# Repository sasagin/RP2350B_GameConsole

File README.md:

For Retrogame
Vtech Creativision  https://github.com/sasagin/Creativision

ColecoVision        https://github.com/sasagin/ColecoRP2350B

SEGA SG1000         https://github.com/sasagin/SG1000

https://github.com/visrealm/pico9918/releases

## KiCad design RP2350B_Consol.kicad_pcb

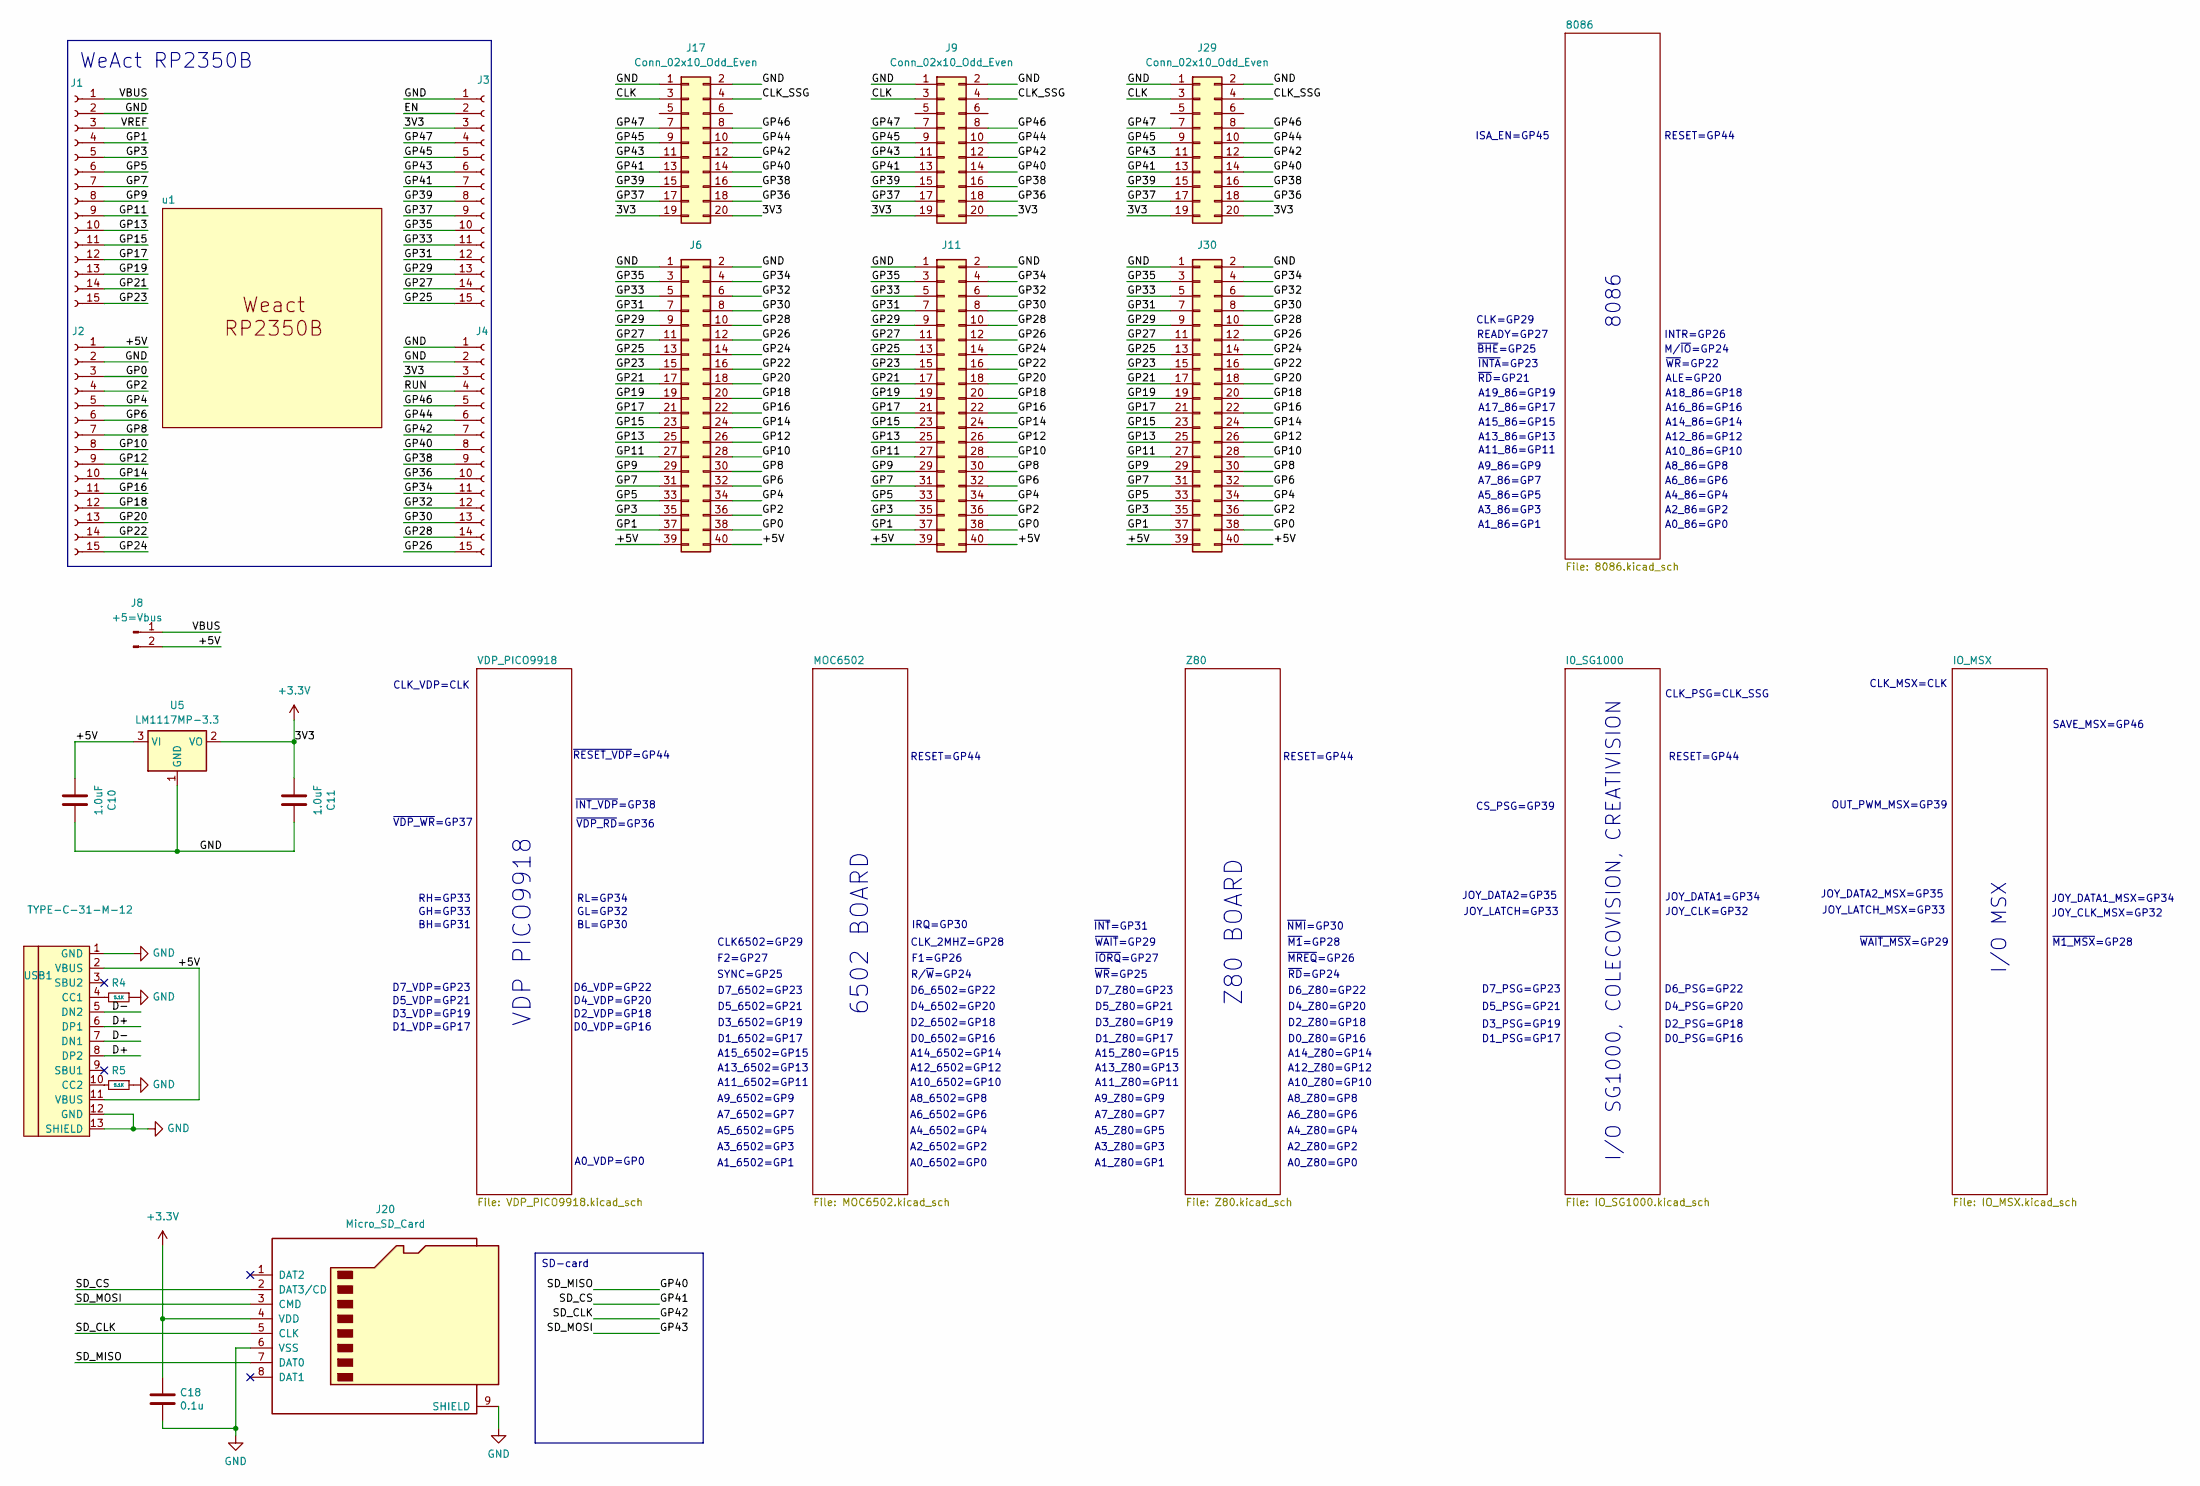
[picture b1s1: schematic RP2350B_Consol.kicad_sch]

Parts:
C10, C11: 1.0uF; C_0805_2012Metric_Pad1.18x1.45mm_HandSolder; DigiKey 1276-1099-1-ND
C18: 0.1u; C_0805_2012Metric_Pad1.18x1.45mm_HandSolder
J1, J2, J3, J4: Conn_01x15_Socket; PinSocket_1x15_P2.54mm_Vertical
J6, J11, J30: Conn_02x20_Odd_Even; PinSocket_2x20_P2.54mm_Vertical
J8: +5=Vbus; PinHeader_1x02_P2.54mm_Vertical
J9, J17, J29: Conn_02x10_Odd_Even; PinSocket_2x10_P2.54mm_Vertical
J20: Micro_SD_Card; GCT-MEM2055-00-190-01-A
R4, R5: 5.1K; R_0805_2012Metric_Pad1.20x1.40mm_HandSolder
U5: LM1117MP-3.3; SOT-223-3_TabPin2
USB1: TYPE-C-31-M-12; USB-TYPE-C-31-M-12_lib2; LCSC C165948
u1: RP2350B_WeAct

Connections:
+3.3V: C11.2, C18.1, J3.3, J4.3, J9.19, J9.20, J17.19, J17.20, J20.4 (VDD), J29.19, J29.20, U5.2 (VO)
/+5V: C10.2, J2.1, J6.39, J6.40, J8.2, J11.39, J11.40, J30.39, J30.40, U5.3 (VI), USB1.2 (VBUS), USB1.11 (VBUS)
/CLK: J9.3, J17.3, J29.3
/CLK_SSG: J9.4, J17.4, J29.4
/D+: USB1.6 (DP1), USB1.8 (DP2)
/D-: USB1.5 (DN2), USB1.7 (DN1)
/EN: J3.2
/GP0: J2.3, J6.38, J11.38, J30.38
/GP1: J1.4, J6.37, J11.37, J30.37
/GP2: J2.4, J6.36, J11.36, J30.36
/GP3: J1.5, J6.35, J11.35, J30.35
/GP4: J2.5, J6.34, J11.34, J30.34
/GP5: J1.6, J6.33, J11.33, J30.33
/GP6: J2.6, J6.32, J11.32, J30.32
/GP7: J1.7, J6.31, J11.31, J30.31
/GP8: J2.7, J6.30, J11.30, J30.30
/GP9: J1.8, J6.29, J11.29, J30.29
/GP10: J2.8, J6.28, J11.28, J30.28
/GP11: J1.9, J6.27, J11.27, J30.27
/GP12: J2.9, J6.26, J11.26, J30.26
/GP13: J1.10, J6.25, J11.25, J30.25
/GP14: J2.10, J6.24, J11.24, J30.24
/GP15: J1.11, J6.23, J11.23, J30.23
/GP16: J2.11, J6.22, J11.22, J30.22
/GP17: J1.12, J6.21, J11.21, J30.21
/GP18: J2.12, J6.20, J11.20, J30.20
/GP19: J1.13, J6.19, J11.19, J30.19
/GP20: J2.13, J6.18, J11.18, J30.18
/GP21: J1.14, J6.17, J11.17, J30.17
/GP22: J2.14, J6.16, J11.16, J30.16
/GP23: J1.15, J6.15, J11.15, J30.15
/GP24: J2.15, J6.14, J11.14, J30.14
/GP25: J3.15, J6.13, J11.13, J30.13
/GP26: J4.15, J6.12, J11.12, J30.12
/GP27: J3.14, J6.11, J11.11, J30.11
/GP28: J4.14, J6.10, J11.10, J30.10
/GP29: J3.13, J6.9, J11.9, J30.9
/GP30: J4.13, J6.8, J11.8, J30.8
/GP31: J3.12, J6.7, J11.7, J30.7
/GP32: J4.12, J6.6, J11.6, J30.6
/GP33: J3.11, J6.5, J11.5, J30.5
/GP34: J4.11, J6.4, J11.4, J30.4
/GP35: J3.10, J6.3, J11.3, J30.3
/GP36: J4.10, J9.18, J17.18, J29.18
/GP37: J3.9, J9.17, J17.17, J29.17
/GP38: J4.9, J9.16, J17.16, J29.16
/GP39: J3.8, J9.15, J17.15, J29.15
/GP40: J4.8, J9.14, J17.14, J20.7 (DAT0), J29.14
/GP41: J3.7, J9.13, J17.13, J20.2 (DAT3/CD), J29.13
/GP42: J4.7, J9.12, J17.12, J20.5 (CLK), J29.12
/GP43: J3.6, J9.11, J17.11, J20.3 (CMD), J29.11
/GP44: J4.6, J9.10, J17.10, J29.10
/GP45: J3.5, J9.9, J17.9, J29.9
/GP46: J4.5, J9.8, J17.8, J29.8
/GP47: J3.4, J9.7, J17.7, J29.7
/RUN: J4.4
/VBUS: J1.1, J8.1
/VREF: J1.3
GND: C10.1, C11.1, C18.2, J1.2, J2.2, J3.1, J4.1, J4.2, J6.1, J6.2, J9.1, J9.2, J11.1, J11.2, J17.1, J17.2, J20.6 (VSS), J20.9 (SHIELD), J29.1, J29.2, J30.1, J30.2, R4.1, R5.1, U5.1 (GND), USB1.1 (GND), USB1.12 (GND), USB1.13 (SHIELD)
unnamed: R4.2, USB1.4 (CC1)
unnamed: R5.2, USB1.10 (CC2)

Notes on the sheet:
WeAct RP2350B
SD-card
A0_Z80=GP0
~{RD}=GP24
~{WR}=GP22
A16_86=GP16
RESET=GP44
A2_86=GP2
A11_6502=GP11
D7_6502=GP23
A0_86=GP0
~{VDP_RD}=GP36
A14_6502=GP14
~{WR}=GP25
RL=GP34
M/~{IO}=GP24
A11_Z80=GP11
A13_6502=GP13
D0_Z80=GP16
D7_VDP=GP23
D3_6502=GP19
Z80 BOARD
D2_6502=GP18
D2_Z80=GP18
~{WAIT_MSX}=GP29
A4_6502=GP4
A15_6502=GP15
SAVE_MSX=GP46
A8_Z80=GP8
A6_6502=GP6
D5_PSG=GP21
JOY_DATA1=GP34
D1_PSG=GP17
CLK6502=GP29
BL=GP30
D5_VDP=GP21
A0_6502=GP0
A18_86=GP18
D4_Z80=GP20
A19_86=GP19

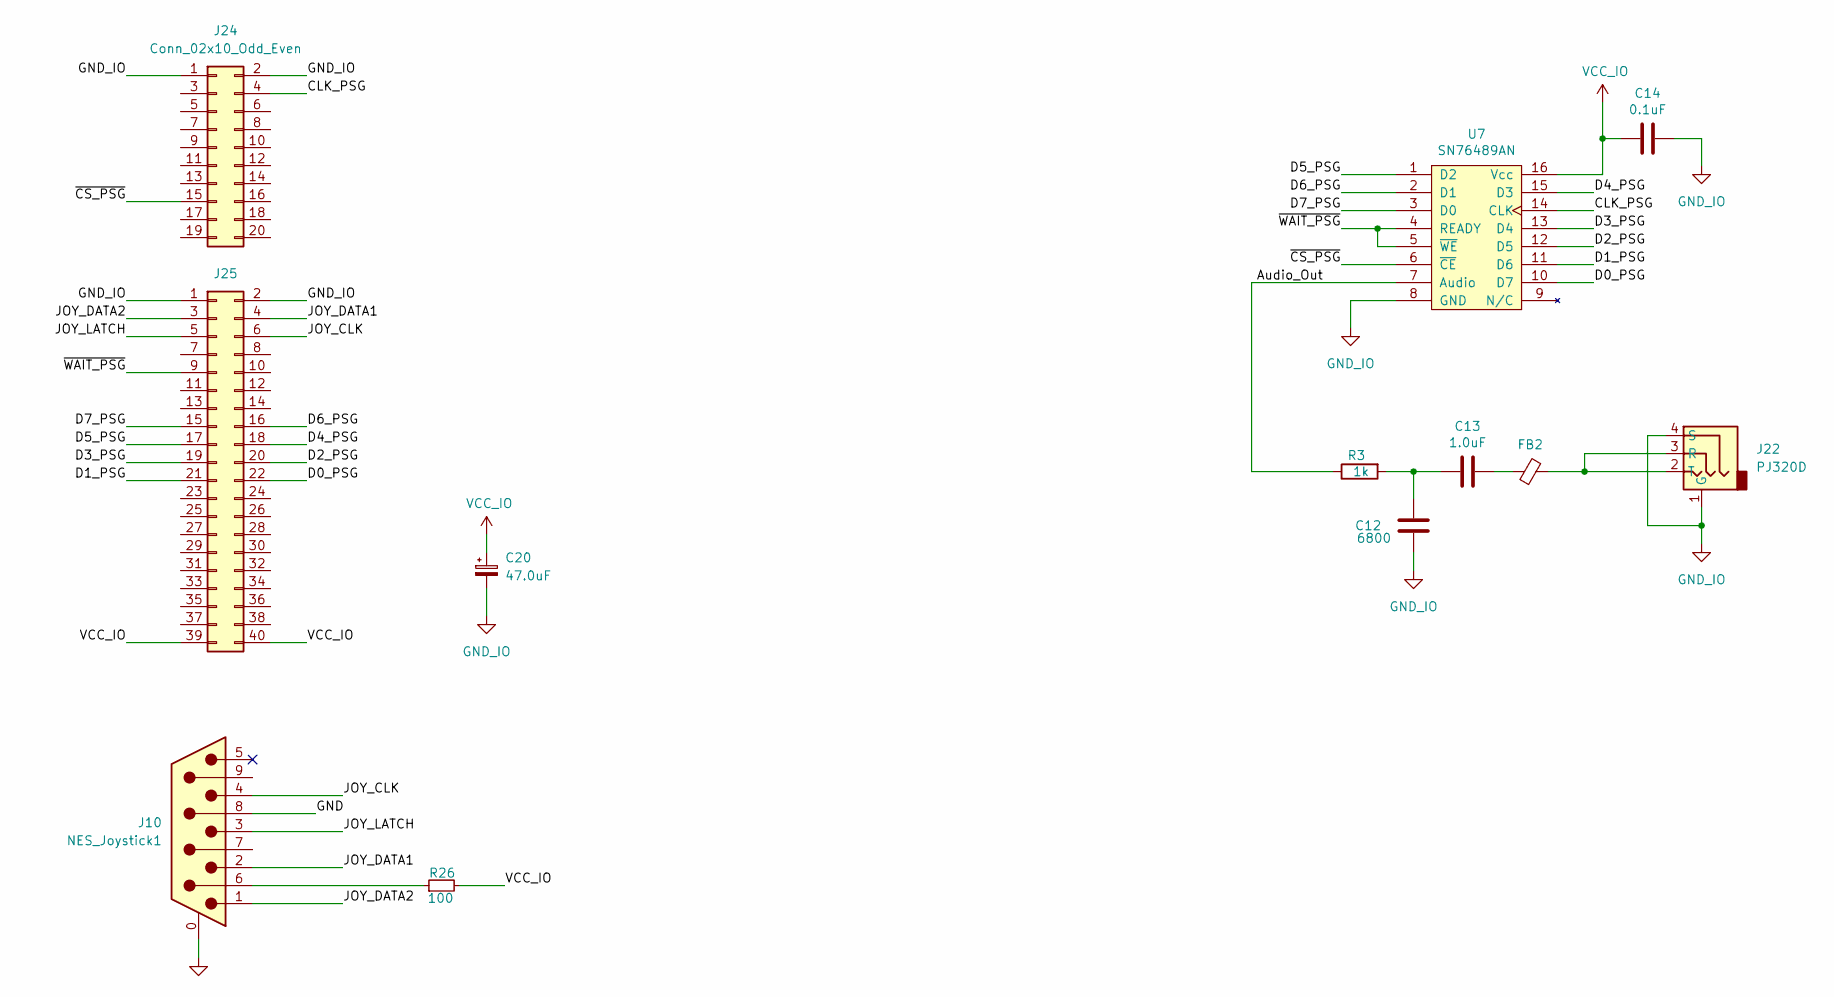
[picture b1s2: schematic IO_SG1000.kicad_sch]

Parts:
C12: 6800; C_0805_2012Metric_Pad1.18x1.45mm_HandSolder; DigiKey 1276-1099-1-ND
C13: 1.0uF; C_0805_2012Metric_Pad1.18x1.45mm_HandSolder; DigiKey 1276-1099-1-ND
C14: 0.1uF; C_0805_2012Metric_Pad1.18x1.45mm_HandSolder; DigiKey 1276-1099-1-ND
C20: 47.0uF; CP_Radial_D5.0mm_P2.00mm
FB2: FerriteBead_Small; L_0805_2012Metric_Pad1.15x1.40mm_HandSolder
J10: NES_Joystick1; DSUB-9_Male_Horizontal_P2.77x2.84mm_EdgePinOffset4.94mm_Hou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
J22: PJ320D; PJ320D_3.5mm_Jack
J24: Conn_02x10_Odd_Even; EDGE_2x10
J25: Conn_02x20_Odd_Even; EDGE_2x20
R3: 1k; R_0805_2012Metric_Pad1.20x1.40mm_HandSolder; DigiKey RMCF0805FT1K00CT-ND
R26: 100; R_0805_2012Metric_Pad1.20x1.40mm_HandSolder
U7: SN76489AN; DIP-16_W7.62mm_LongPads; DigiKey AE9992-ND

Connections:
/I0_SG1000/Audio_Out: R3.1, U7.7 (Audio)
/I0_SG1000/CLK_PSG: J24.4, U7.14 (CLK)
/I0_SG1000/D0_PSG: J25.22, U7.10 (D7)
/I0_SG1000/D1_PSG: J25.21, U7.11 (D6)
/I0_SG1000/D2_PSG: J25.20, U7.12 (D5)
/I0_SG1000/D3_PSG: J25.19, U7.13 (D4)
/I0_SG1000/D4_PSG: J25.18, U7.15 (D3)
/I0_SG1000/D5_PSG: J25.17, U7.1 (D2)
/I0_SG1000/D6_PSG: J25.16, U7.2 (D1)
/I0_SG1000/D7_PSG: J25.15, U7.3 (D0)
/I0_SG1000/GND: J10.8
/I0_SG1000/JOY_CLK: J10.4, J25.6
/I0_SG1000/JOY_DATA1: J10.2, J25.4
/I0_SG1000/JOY_DATA2: J10.1, J25.3
/I0_SG1000/JOY_LATCH: J10.3, J25.5
/I0_SG1000/~CS_PSG: J24.15, U7.6 (~CE)
/I0_SG1000/~WAIT_PSG: J24.5, J25.9, U7.4 (READY), U7.5 (~WE)
GND_IO: C12.2, C14.1, C20.2, J10.0 (PAD), J22.1 (G), J22.4 (S), J24.1, J24.2, J25.1, J25.2, U7.8 (GND)
unnamed: C12.1, C13.2, R3.2
unnamed: C13.1, FB2.1
unnamed: J10.6, R26.1
unnamed: FB2.2, J22.2 (T), J22.3 (R)
VCC_IO: C14.2, C20.1, J25.39, J25.40, R26.2, U7.16 (Vcc)

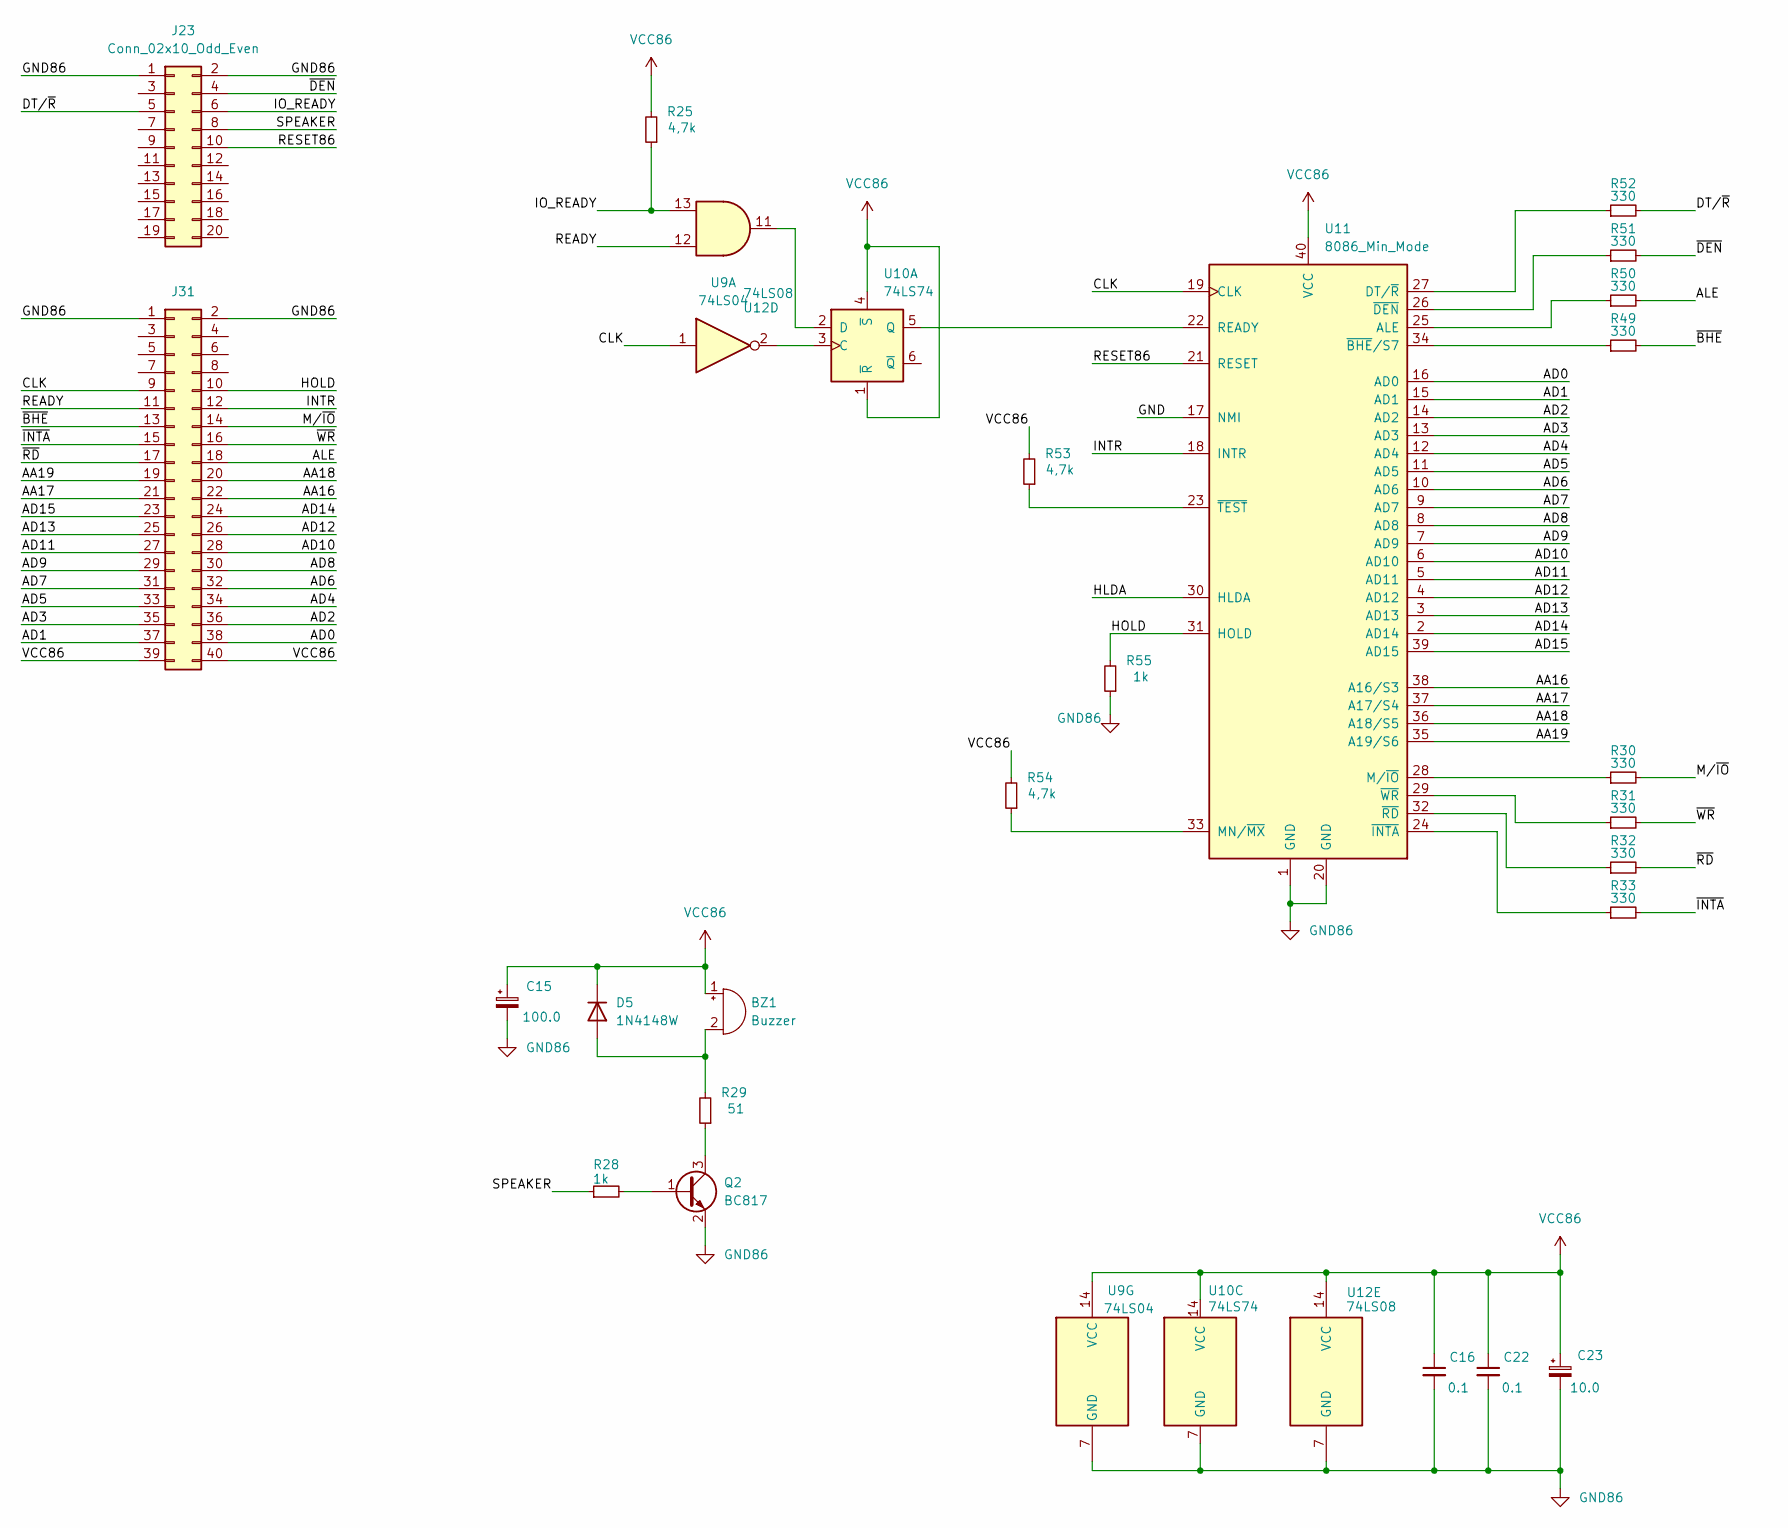
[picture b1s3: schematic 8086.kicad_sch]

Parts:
BZ1: Buzzer; Buzzer_12x9.5RM7.6
C15: 100.0; CP_Radial_D6.3mm_P2.50mm
C16, C22: 0.1; C_0805_2012Metric_Pad1.18x1.45mm_HandSolder
C23: 10.0; CP_Radial_D4.0mm_P1.50mm
D5: 1N4148W; D_SOD-123
J23: Conn_02x10_Odd_Even; EDGE_2x10
J31: Conn_02x20_Odd_Even; EDGE_2x20
Q2: BC817; SOT-23
R25, R53, R54: 4,7k; R_0805_2012Metric_Pad1.20x1.40mm_HandSolder
R28, R55: 1k; R_0805_2012Metric_Pad1.20x1.40mm_HandSolder
R29: 51; R_0805_2012Metric_Pad1.20x1.40mm_HandSolder
R30, R31, R32, R33, R49, R50, R51, R52: 330; R_0805_2012Metric_Pad1.20x1.40mm_HandSolder
U9: 74LS04; SOIC-14_3.9x8.7mm_P1.27mm
U10: 74LS74
U11: 8086_Min_Mode; DIP-40_W15.24mm
U12: 74LS08; SOIC-14_3.9x8.7mm_P1.27mm

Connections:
/8086/AA16: J31.22, U11.38 (A16/S3)
/8086/AA17: J31.21, U11.37 (A17/S4)
/8086/AA18: J31.20, U11.36 (A18/S5)
/8086/AA19: J31.19, U11.35 (A19/S6)
/8086/AD0: J31.38, U11.16 (AD0)
/8086/AD1: J31.37, U11.15 (AD1)
/8086/AD2: J31.36, U11.14 (AD2)
/8086/AD3: J31.35, U11.13 (AD3)
/8086/AD4: J31.34, U11.12 (AD4)
/8086/AD5: J31.33, U11.11 (AD5)
/8086/AD6: J31.32, U11.10 (AD6)
/8086/AD7: J31.31, U11.9 (AD7)
/8086/AD8: J31.30, U11.8 (AD8)
/8086/AD9: J31.29, U11.7 (AD9)
/8086/AD10: J31.28, U11.6 (AD10)
/8086/AD11: J31.27, U11.5 (AD11)
/8086/AD12: J31.26, U11.4 (AD12)
/8086/AD13: J31.25, U11.3 (AD13)
/8086/AD14: J31.24, U11.2 (AD14)
/8086/AD15: J31.23, U11.39 (AD15)
/8086/ALE: J31.18, R50.2
/8086/CLK: J31.9, U9.1, U11.19 (CLK)
/8086/DT/~R: J23.5, R52.2
/8086/GND: U11.17 (NMI)
/8086/HLDA: U11.30 (HLDA)
/8086/HOLD: J31.10, R55.2, U11.31 (HOLD)
/8086/INTR: J31.12, U11.18 (INTR)
/8086/IO_READY: J23.6, R25.1, U12.13
/8086/M/~IO: J31.14, R30.2
/8086/READY: J31.11, U12.12
/8086/RESET86: J23.10, U11.21 (RESET)
/8086/SPEAKER: J23.8, R28.1
/8086/~BHE: J31.13, R49.2
/8086/~DEN: J23.4, R51.2
/8086/~INTA: J31.15, R33.2
/8086/~RD: J31.17, R32.2
/8086/~WR: J31.16, R31.2
GND86: C15.2, C16.2, C22.2, C23.2, J23.1, J23.2, J31.1, J31.2, Q2.2 (E), R55.1, U9.7 (GND), U10.7 (GND), U11.1 (GND), U11.20 (GND), U12.7 (GND)
unnamed: BZ1.2 (-), D5.2 (A), R29.2
unnamed: Q2.1 (B), R28.2
unnamed: Q2.3 (C), R29.1
unnamed: U9.2, U10.3 (C)
unnamed: U10.2 (D), U12.11
unnamed: U10.5 (Q), U11.22 (READY)
unnamed: R50.1, U11.25 (ALE)
unnamed: R52.1, U11.27 (DT/~R)
unnamed: R54.1, U11.33 (MN/~MX)
unnamed: R30.1, U11.28 (M/~IO)
unnamed: R49.1, U11.34 (~BHE/S7)
unnamed: R51.1, U11.26 (~DEN)
unnamed: R33.1, U11.24 (~INTA)
unnamed: R32.1, U11.32 (~RD)
unnamed: R53.1, U11.23 (~TEST)
unnamed: R31.1, U11.29 (~WR)
VCC86: BZ1.1 (+), C15.1, C16.1, C22.1, C23.1, D5.1 (K), J31.39, J31.40, R25.2, R53.2, R54.2, U9.14 (VCC), U10.1 (~R), U10.4 (~S), U10.14 (VCC), U11.40 (VCC), U12.14 (VCC)

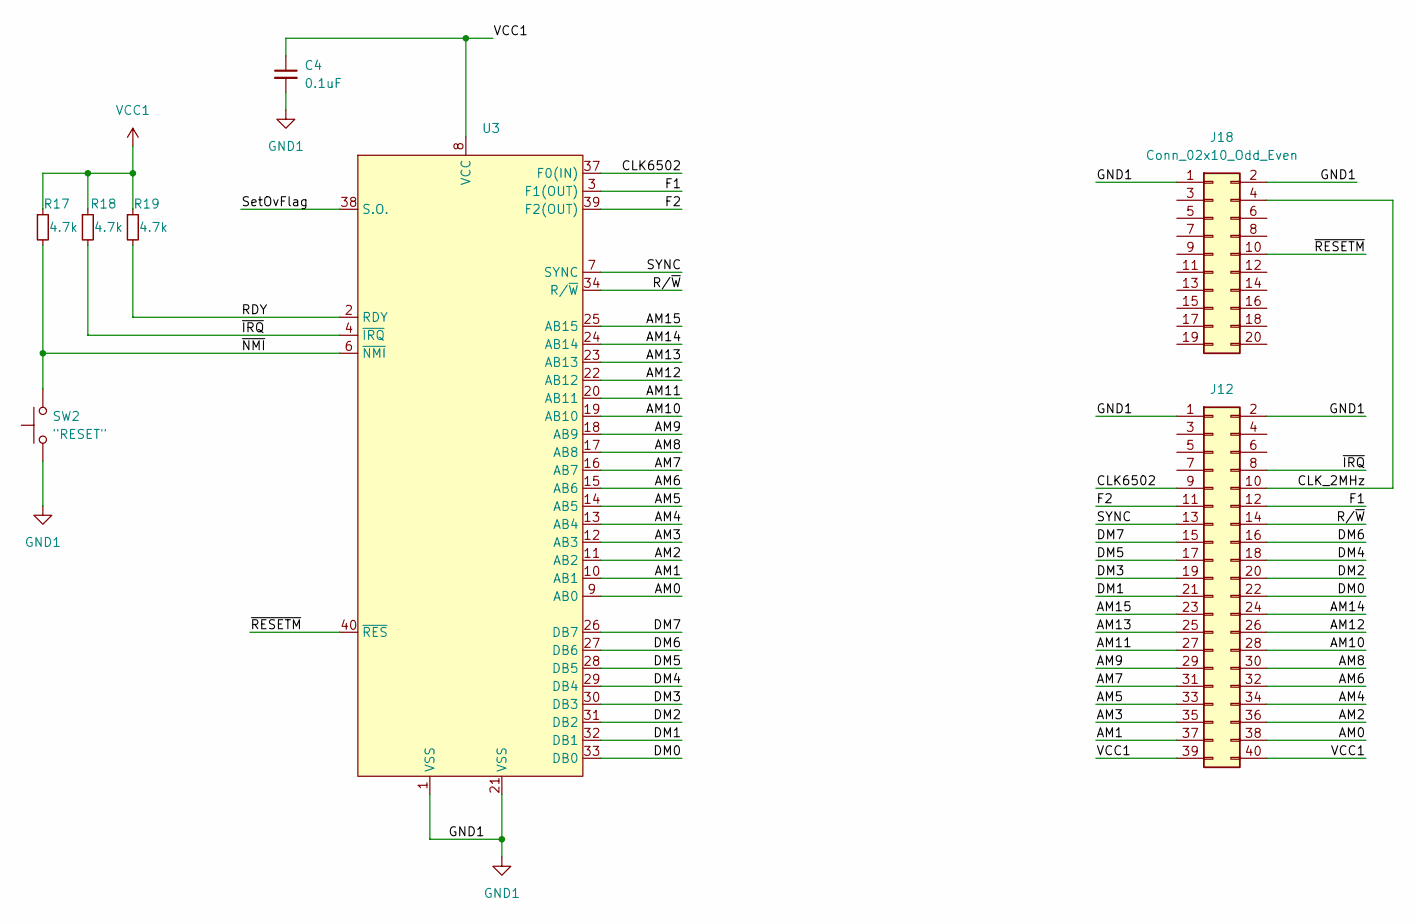
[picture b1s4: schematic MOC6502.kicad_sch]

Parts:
C4: 0.1uF; C_0805_2012Metric_Pad1.18x1.45mm_HandSolder
J12: Conn_02x20_Odd_Even; EDGE_2x20
J18: Conn_02x10_Odd_Even; EDGE_2x10
R17, R18, R19: 4.7k; R_0805_2012Metric_Pad1.20x1.40mm_HandSolder
SW2: "RESET"; SW_Tactile_SPST_Angled_PTS645Vx31-2LFS
U3: DIP-40_W15.24mm_Socket

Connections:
/MOC6502/AM0: J12.38, U3.9 (AB0)
/MOC6502/AM1: J12.37, U3.10 (AB1)
/MOC6502/AM2: J12.36, U3.11 (AB2)
/MOC6502/AM3: J12.35, U3.12 (AB3)
/MOC6502/AM4: J12.34, U3.13 (AB4)
/MOC6502/AM5: J12.33, U3.14 (AB5)
/MOC6502/AM6: J12.32, U3.15 (AB6)
/MOC6502/AM7: J12.31, U3.16 (AB7)
/MOC6502/AM8: J12.30, U3.17 (AB8)
/MOC6502/AM9: J12.29, U3.18 (AB9)
/MOC6502/AM10: J12.28, U3.19 (AB10)
/MOC6502/AM11: J12.27, U3.20 (AB11)
/MOC6502/AM12: J12.26, U3.22 (AB12)
/MOC6502/AM13: J12.25, U3.23 (AB13)
/MOC6502/AM14: J12.24, U3.24 (AB14)
/MOC6502/AM15: J12.23, U3.25 (AB15)
/MOC6502/CLK6502: J12.9, U3.37 (F0(IN))
/MOC6502/CLK_2MHz: J12.10, J18.4
/MOC6502/DM0: J12.22, U3.33 (DB0)
/MOC6502/DM1: J12.21, U3.32 (DB1)
/MOC6502/DM2: J12.20, U3.31 (DB2)
/MOC6502/DM3: J12.19, U3.30 (DB3)
/MOC6502/DM4: J12.18, U3.29 (DB4)
/MOC6502/DM5: J12.17, U3.28 (DB5)
/MOC6502/DM6: J12.16, U3.27 (DB6)
/MOC6502/DM7: J12.15, U3.26 (DB7)
/MOC6502/F1: J12.12, U3.3 (F1(OUT))
/MOC6502/F2: J12.11, U3.39 (F2(OUT))
/MOC6502/RDY: R19.2, U3.2 (RDY)
/MOC6502/R/~W: J12.14, U3.34 (R/~W)
/MOC6502/SYNC: J12.13, U3.7 (SYNC)
/MOC6502/SetOvFlag: U3.38 (S.O.)
/MOC6502/~IRQ: J12.8, R18.2, U3.4 (~IRQ)
/MOC6502/~NMI: R17.2, SW2.2, U3.6 (~NMI)
/MOC6502/~RESETM: J18.10, U3.40 (~RES)
GND1: C4.2, J12.1, J12.2, J18.1, J18.2, SW2.1, U3.1 (VSS), U3.21 (VSS)
VCC1: C4.1, J12.39, J12.40, R17.1, R18.1, R19.1, U3.8 (VCC)

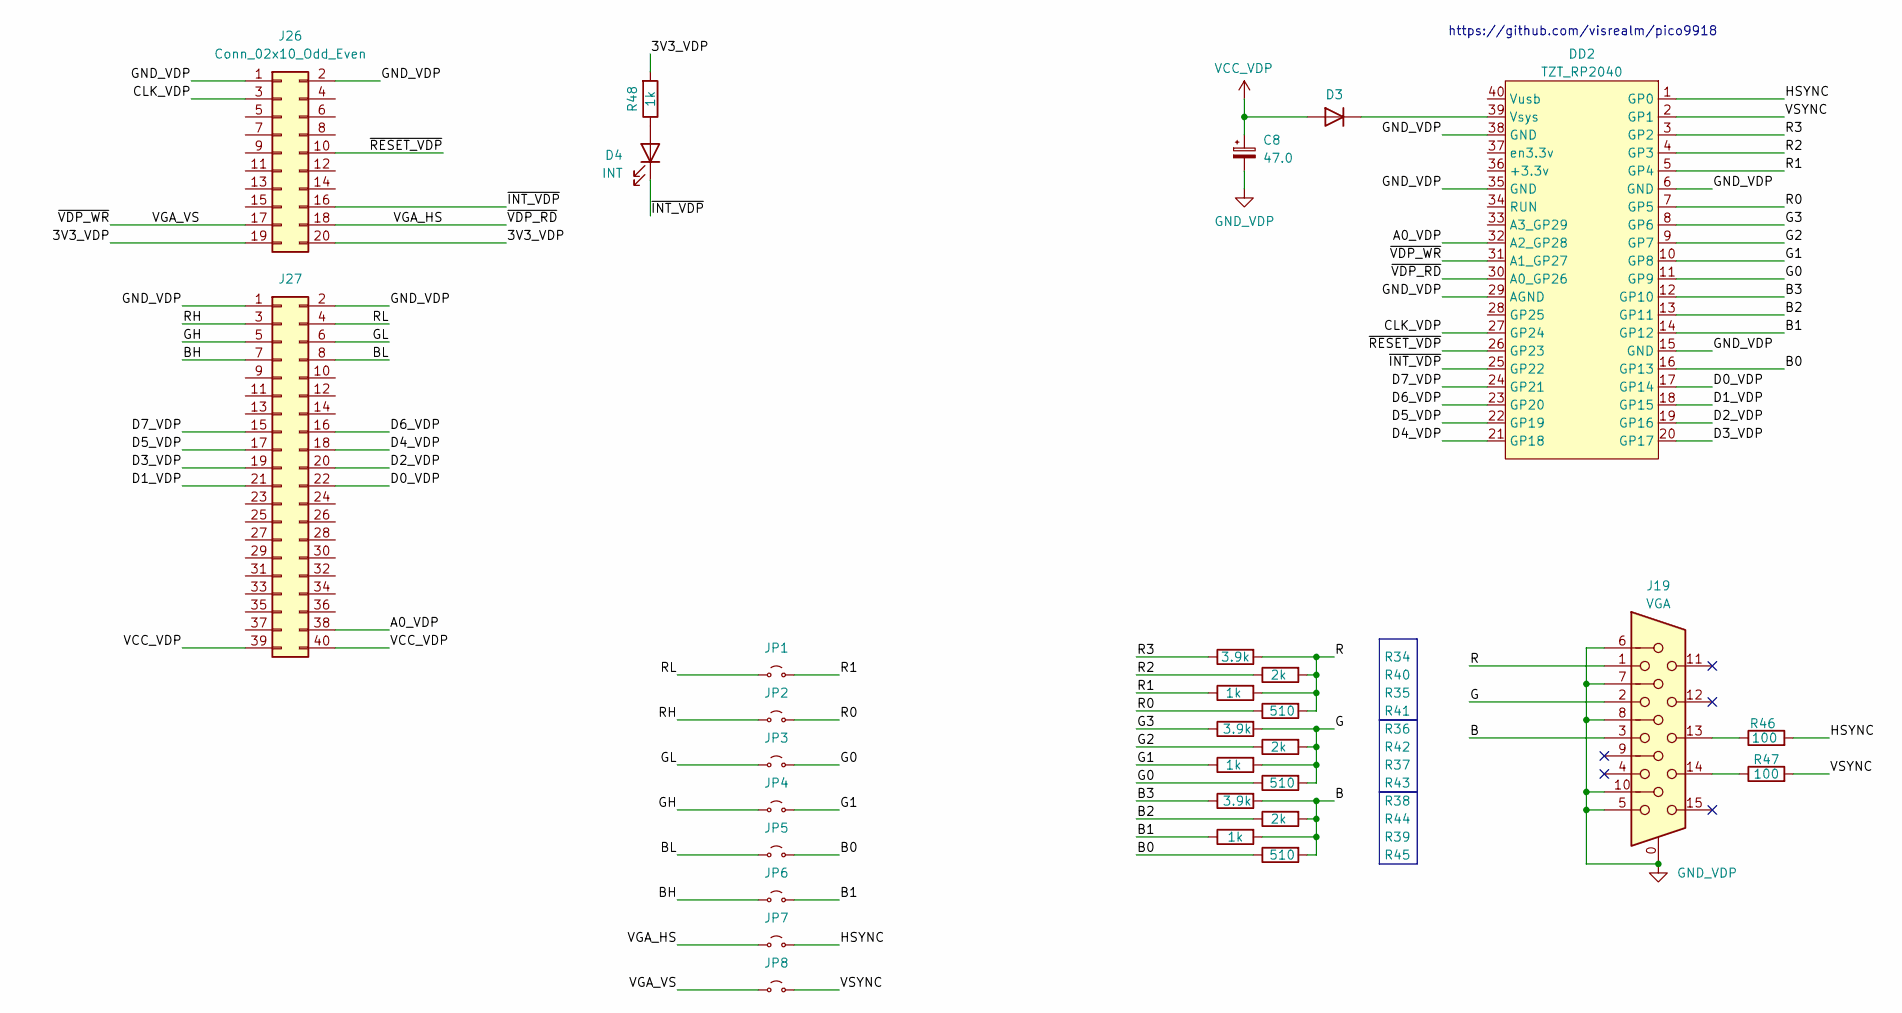
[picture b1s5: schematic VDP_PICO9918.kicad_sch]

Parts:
C8: 47.0; CP_Radial_D5.0mm_P2.50mm
D3: D; D_1206_3216Metric_Pad1.42x1.75mm_HandSolder; DigiKey 641-1310-1-ND
D4: INT; LED_D2.0mm_W4.8mm_H2.5mm_FlatTop
DD2: TZT_RP2040; RP2040_purple_allPin
J19: VGA; DSUB-15-HD_Female_Horizontal_P2.29x1.98mm_EdgePinOffset3.03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
J26: Conn_02x10_Odd_Even; EDGE_2x10
J27: Conn_02x20_Odd_Even; EDGE_2x20
JP1, JP2, JP3, JP4, JP5, JP6, JP7, JP8: Jumper_2_Small_Open; PinHeader_1x02_P2.54mm_Vertical
R34, R36, R38: 3.9k; R_0805_2012Metric_Pad1.20x1.40mm_HandSolder; DigiKey RMCF0805JT100RCT-ND
R35, R37, R39, R48: 1k; R_0805_2012Metric_Pad1.20x1.40mm_HandSolder; DigiKey RMCF0805JT100RCT-ND
R40, R42, R44: 2k; R_0805_2012Metric_Pad1.20x1.40mm_HandSolder; DigiKey RMCF0805JT100RCT-ND
R41, R43, R45: 510; R_0805_2012Metric_Pad1.20x1.40mm_HandSolder; DigiKey RMCF0805JT100RCT-ND
R46, R47: 100; R_0805_2012Metric_Pad1.20x1.40mm_HandSolder

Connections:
/VDP_PICO9918/3V3_VDP: J26.19, J26.20, R48.2
/VDP_PICO9918/A0_VDP: DD2.32 (A2_GP28), J27.38
/VDP_PICO9918/B: J19.3, R38.2, R39.2, R44.2, R45.2
/VDP_PICO9918/B0: DD2.16 (GP13), JP5.2 (B), R45.1
/VDP_PICO9918/B1: DD2.14 (GP12), JP6.2 (B), R39.1
/VDP_PICO9918/B2: DD2.13 (GP11), R44.1
/VDP_PICO9918/B3: DD2.12 (GP10), R38.1
/VDP_PICO9918/BH: J27.7, JP6.1 (A)
/VDP_PICO9918/BL: J27.8, JP5.1 (A)
/VDP_PICO9918/CLK_VDP: DD2.27 (GP24), J26.3
/VDP_PICO9918/D0_VDP: DD2.17 (GP14), J27.22
/VDP_PICO9918/D1_VDP: DD2.18 (GP15), J27.21
/VDP_PICO9918/D2_VDP: DD2.19 (GP16), J27.20
/VDP_PICO9918/D3_VDP: DD2.20 (GP17), J27.19
/VDP_PICO9918/D4_VDP: DD2.21 (GP18), J27.18
/VDP_PICO9918/D5_VDP: DD2.22 (GP19), J27.17
/VDP_PICO9918/D6_VDP: DD2.23 (GP20), J27.16
/VDP_PICO9918/D7_VDP: DD2.24 (GP21), J27.15
/VDP_PICO9918/G: J19.2, R36.2, R37.2, R42.2, R43.2
/VDP_PICO9918/G0: DD2.11 (GP9), JP3.2 (B), R43.1
/VDP_PICO9918/G1: DD2.10 (GP8), JP4.2 (B), R37.1
/VDP_PICO9918/G2: DD2.9 (GP7), R42.1
/VDP_PICO9918/G3: DD2.8 (GP6), R36.1
/VDP_PICO9918/GH: J27.5, JP4.1 (A)
/VDP_PICO9918/GL: J27.6, JP3.1 (A)
/VDP_PICO9918/HSYNC: DD2.1 (GP0), JP7.2 (B), R46.2
/VDP_PICO9918/R: J19.1, R34.2, R35.2, R40.2, R41.2
/VDP_PICO9918/R0: DD2.7 (GP5), JP2.2 (B), R41.1
/VDP_PICO9918/R1: DD2.5 (GP4), JP1.2 (B), R35.1
/VDP_PICO9918/R2: DD2.4 (GP3), R40.1
/VDP_PICO9918/R3: DD2.3 (GP2), R34.1
/VDP_PICO9918/RH: J27.3, JP2.1 (A)
/VDP_PICO9918/RL: J27.4, JP1.1 (A)
/VDP_PICO9918/VGA_HS: DD2.30 (A0_GP26), J26.18, JP7.1 (A)
/VDP_PICO9918/VGA_VS: DD2.31 (A1_GP27), J26.17, JP8.1 (A)
/VDP_PICO9918/VSYNC: DD2.2 (GP1), JP8.2 (B), R47.2
/VDP_PICO9918/~INT_VDP: D4.1 (K), DD2.25 (GP22), J26.16
/VDP_PICO9918/~RESET_VDP: DD2.26 (GP23), J26.10
GND_VDP: C8.2, DD2.6 (GND), DD2.15 (GND), DD2.29 (AGND), DD2.35 (GND), DD2.38 (GND), J19.0, J19.5, J19.6, J19.7, J19.8, J19.10, J26.1, J26.2, J27.1, J27.2
unnamed: D3.1 (K), DD2.39 (Vsys)
unnamed: D4.2 (A), R48.1
unnamed: J19.13, R46.1
unnamed: J19.14, R47.1
VCC_VDP: C8.1, D3.2 (A), J27.39, J27.40

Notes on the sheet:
https://github.com/visrealm/pico9918

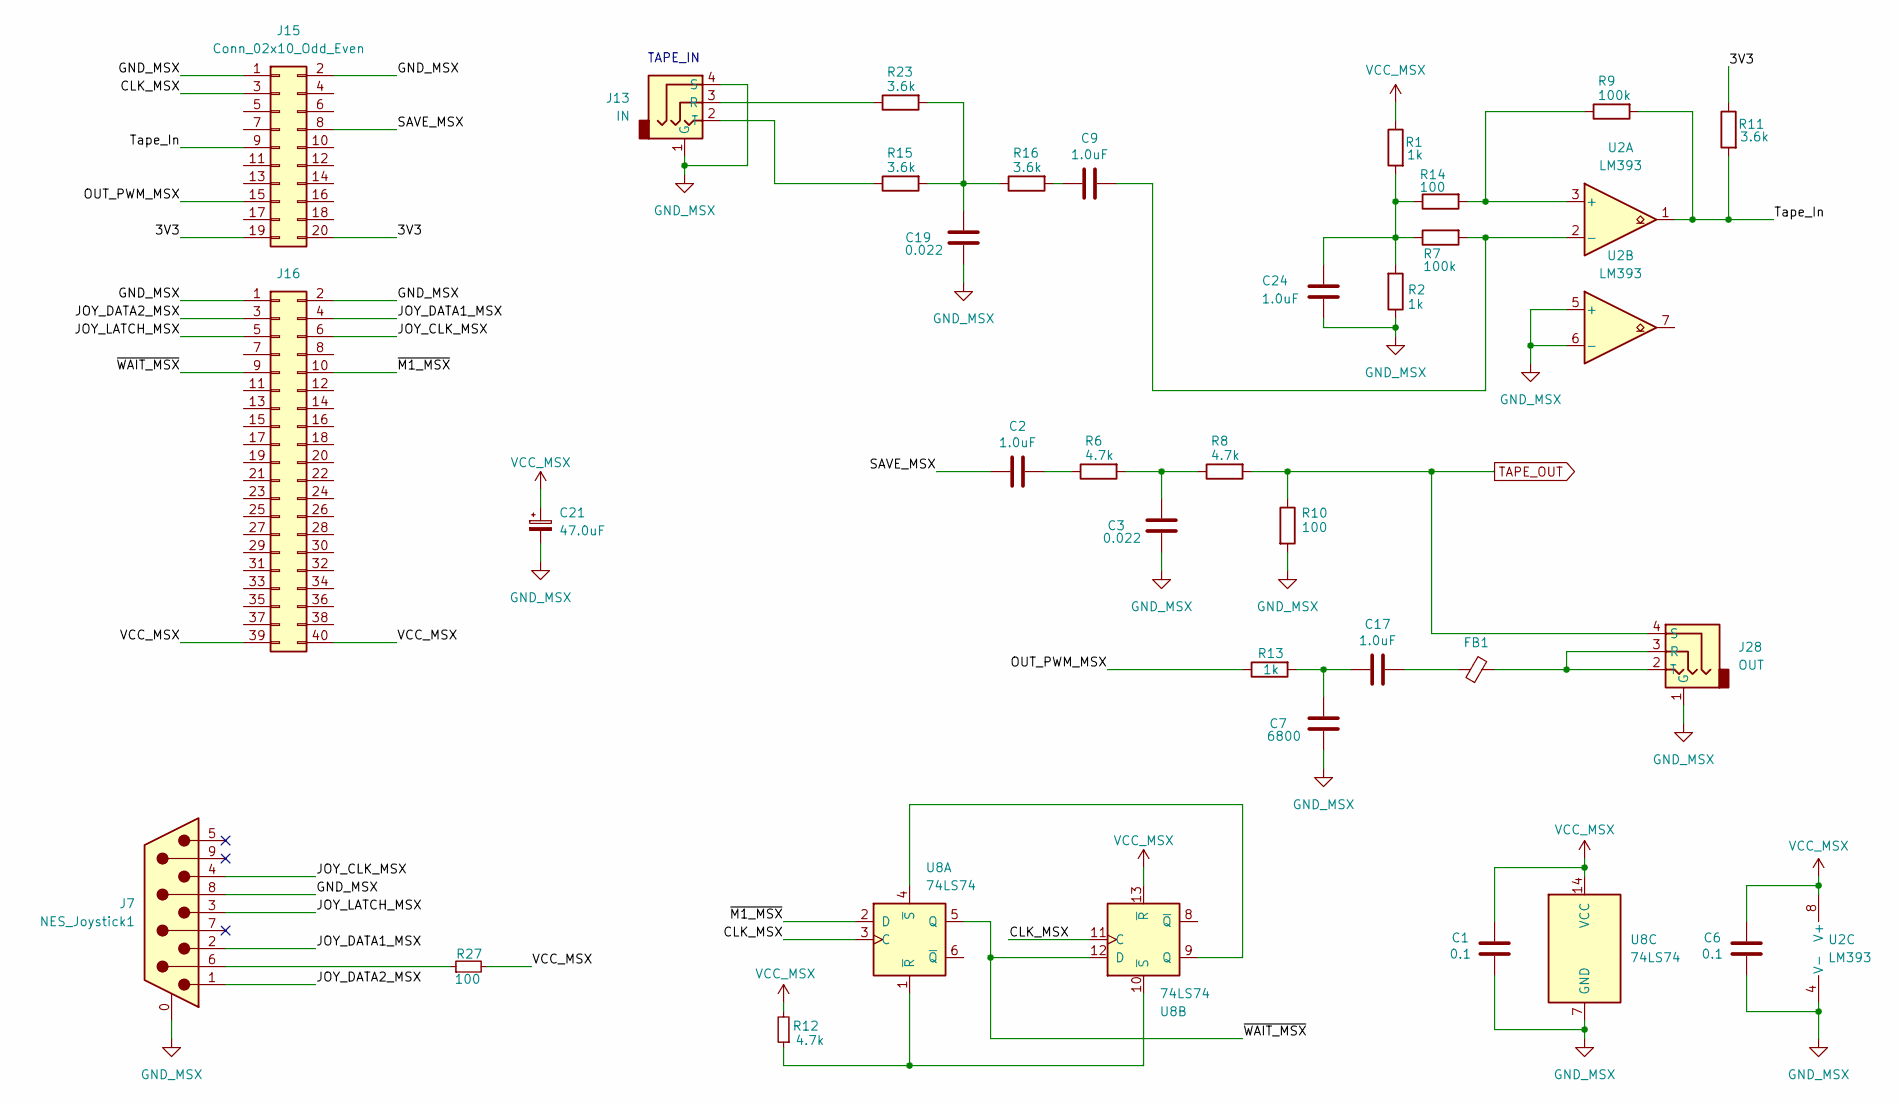
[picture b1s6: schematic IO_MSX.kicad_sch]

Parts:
C1, C6: 0.1; C_0805_2012Metric_Pad1.18x1.45mm_HandSolder; DigiKey 1276-1099-1-ND
C2, C9, C17, C24: 1.0uF; C_0805_2012Metric_Pad1.18x1.45mm_HandSolder; DigiKey 1276-1099-1-ND
C3, C19: 0.022; C_0805_2012Metric_Pad1.18x1.45mm_HandSolder; DigiKey 1276-1099-1-ND
C7: 6800; C_0805_2012Metric_Pad1.18x1.45mm_HandSolder; DigiKey 1276-1099-1-ND
C21: 47.0uF; CP_Radial_D5.0mm_P2.00mm
FB1: FerriteBead_Small; L_0805_2012Metric_Pad1.15x1.40mm_HandSolder
J7: NES_Joystick1; DSUB-9_Male_Horizontal_P2.77x2.84mm_EdgePinOffset4.94mm_Hou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
J13: IN; PJ320D_3.5mm_Jack
J15: Conn_02x10_Odd_Even; EDGE_2x10
J16: Conn_02x20_Odd_Even; EDGE_2x20
J28: OUT; PJ320D_3.5mm_Jack
R1, R2, R13: 1k; R_0805_2012Metric_Pad1.20x1.40mm_HandSolder; DigiKey RMCF0805FT1K00CT-ND
R6, R8: 4.7k; R_0805_2012Metric_Pad1.20x1.40mm_HandSolder; DigiKey RMCF0805FT1K00CT-ND
R7, R9: 100k; R_0805_2012Metric_Pad1.20x1.40mm_HandSolder; DigiKey RMCF0805FT1K00CT-ND
R10, R27: 100; R_0805_2012Metric_Pad1.20x1.40mm_HandSolder
R11, R15, R16, R23: 3.6k; R_0805_2012Metric_Pad1.20x1.40mm_HandSolder; DigiKey RMCF0805FT1K00CT-ND
R12: 4.7k; R_0805_2012Metric_Pad1.20x1.40mm_HandSolder
R14: 100; R_0805_2012Metric_Pad1.20x1.40mm_HandSolder; DigiKey RMCF0805FT1K00CT-ND
U2: LM393; SOIC-8_3.9x4.9mm_P1.27mm
U8: 74LS74; SOIC-14_3.9x8.7mm_P1.27mm

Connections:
/IO_MSX/3V3: J15.19, J15.20, R11.1
/IO_MSX/CLK_MSX: J15.3, U8.3 (C), U8.11 (C)
/IO_MSX/JOY_CLK_MSX: J7.4, J16.6
/IO_MSX/JOY_DATA1_MSX: J7.2, J16.4
/IO_MSX/JOY_DATA2_MSX: J7.1, J16.3
/IO_MSX/JOY_LATCH_MSX: J7.3, J16.5
/IO_MSX/OUT_PWM_MSX: J15.15, R13.1
/IO_MSX/SAVE_MSX: C2.2, J15.8
/IO_MSX/Tape_In: J15.9, R9.2, R11.2, U2.1
/IO_MSX/~M1_MSX: J16.10, U8.2 (D)
/IO_MSX/~WAIT_MSX: J16.9, U8.5 (Q), U8.12 (D)
GND_MSX: C1.2, C3.2, C6.2, C7.2, C19.2, C21.2, C24.2, J7.0 (PAD), J7.8, J13.1 (G), J13.4 (S), J15.1, J15.2, J16.1, J16.2, J28.1 (G), R2.1, R10.2, U2.4 (V-), U2.5 (+), U2.6 (-), U8.7 (GND); also elsewhere on the board
unnamed: C2.1, R6.1
unnamed: C3.1, R6.2, R8.1
unnamed: C9.2, R16.2
unnamed: C17.1, FB1.1
unnamed: C7.1, C17.2, R13.2
unnamed: C19.1, R15.2, R16.1, R23.2
unnamed: C24.1, R1.2, R2.2, R7.1, R14.1
unnamed: J7.6, R27.1
unnamed: J13.3 (R), R23.1
unnamed: J13.2 (T), R15.1
unnamed: FB1.2, J28.2 (T), J28.3 (R)
unnamed: R9.1, R14.2, U2.3 (+)
unnamed 262: C9.1, R7.2, U2.2 (-); also elsewhere on the board
unnamed: R12.1, U8.1 (~R), U8.10 (~S)
unnamed: U8.4 (~S), U8.9 (Q)
TAPE_OUT: J28.4 (S), R8.2, R10.1
VCC_MSX: C1.1, C6.1, C21.1, J16.39, J16.40, R1.1, R12.2, R27.2, U2.8 (V+), U8.13 (~R), U8.14 (VCC)

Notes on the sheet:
TAPE_IN
